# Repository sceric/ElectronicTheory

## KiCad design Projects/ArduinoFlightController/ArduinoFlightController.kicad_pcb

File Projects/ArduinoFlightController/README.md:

# ArduinoFlightController
Flight controller hardware using mulitiwii firmware

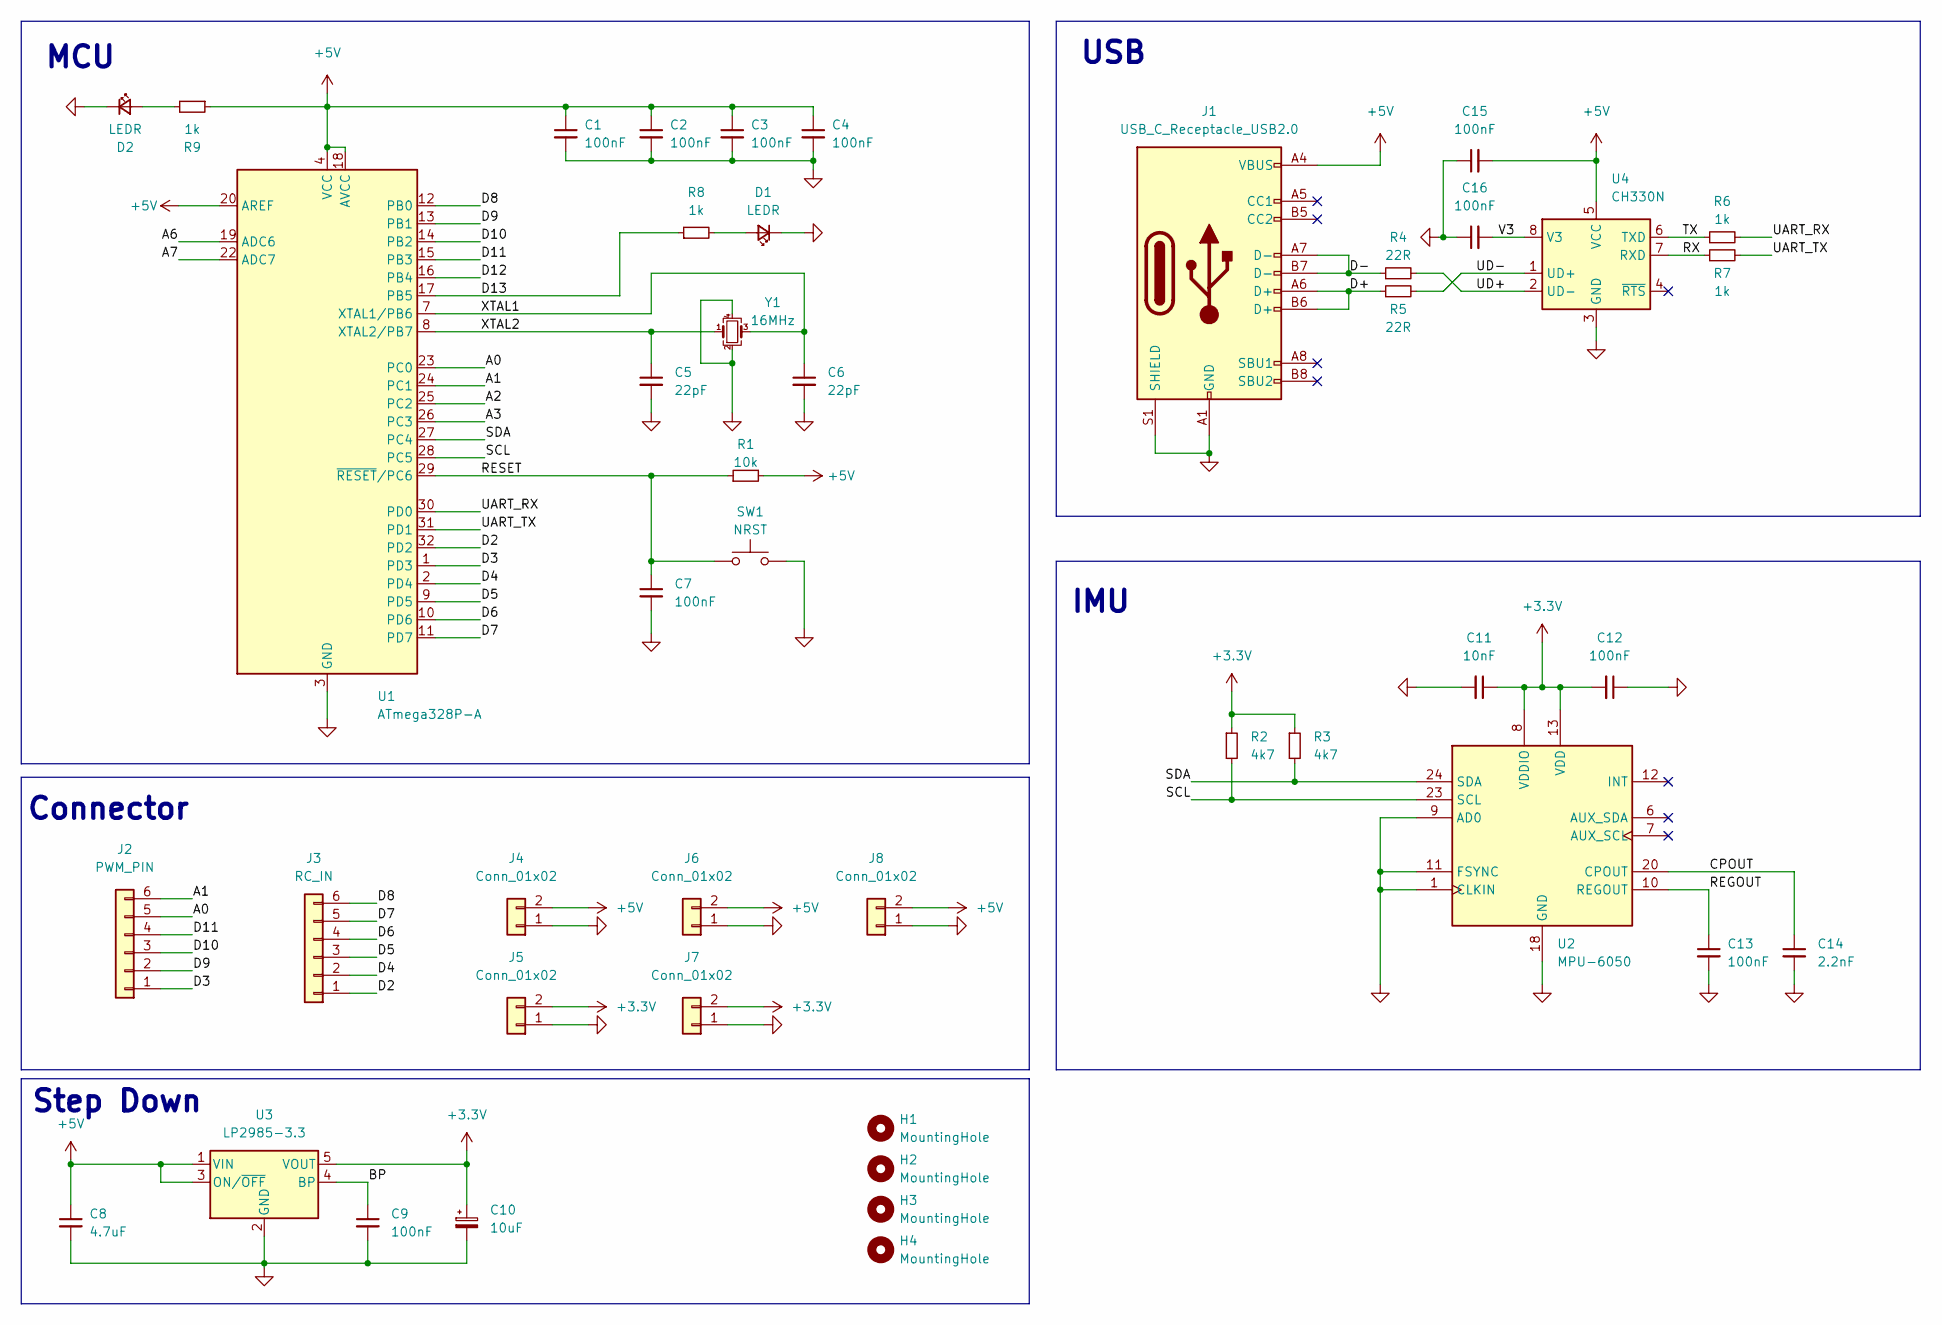
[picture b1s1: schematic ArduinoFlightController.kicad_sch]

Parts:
C1, C2, C3, C4, C7, C9, C12, C13, C15, C16: 100nF; C_0603_1608Metric
C5, C6: 22pF; C_0603_1608Metric
C8: 4.7uF; C_0805_2012Metric
C10: 10uF; CP_EIA-3216-10_Kemet-I
C11: 10nF; C_0603_1608Metric
C14: 2.2nF; C_0603_1608Metric
D1, D2: LEDR; LED_0603_1608Metric
H1, H2, H3, H4: MountingHole; MountingHole_3mm_Pad_Via
J1: USB_C_Receptacle_USB2.0; USB_C_Receptacle_XKB_U262-16XN-4BVC11
J2: PWM_PIN; pad_01x06
J3: RC_IN; pad_01x06
J4, J5, J6, J7, J8: Conn_01x02; pad_01x02
R1: 10k; R_0603_1608Metric
R2, R3: 4k7; R_0603_1608Metric
R4, R5: 22R; R_0603_1608Metric
R6, R7, R8, R9: 1k; R_0603_1608Metric
SW1: NRST; SW_SPST_B3U-1000P
U1: ATmega328P-A; TQFP-32_7x7mm_P0.8mm
U2: MPU-6050; InvenSense_QFN-24_4x4mm_P0.5mm
U3: LP2985-3.3; SOT-23-5
U4: CH330N; SOIC-8_3.9x4.9mm_P1.27mm
Y1: 16MHz; Crystal_SMD_3225-4Pin_3.2x2.5mm

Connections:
+3V3: C10.1, C11.1, C12.2, J5.2, J7.2, R2.1, R3.1, U2.8 (VDDIO), U2.13 (VDD), U3.5 (VOUT)
+5V: C1.1, C2.1, C3.1, C4.1, C8.1, C15.2, J1.A4 (VBUS), J1.A9 (VBUS), J1.B4 (VBUS), J1.B9 (VBUS), J4.2, J6.2, J8.2, R1.2, R9.1, U1.4 (VCC), U1.6 (VCC), U1.18 (AVCC), U1.20 (AREF), U3.1 (VIN), U3.3 (ON/~OFF), U4.5 (VCC)
/A0: J2.5, U1.23 (PC0)
/A1: J2.6, U1.24 (PC1)
/A2: U1.25 (PC2)
/A3: U1.26 (PC3)
/A6: U1.19 (ADC6)
/A7: U1.22 (ADC7)
/BP: C9.1, U3.4 (BP)
/CPOUT: C14.1, U2.20 (CPOUT)
/D2: J3.1, U1.32 (PD2)
/D3: J2.1, U1.1 (PD3)
/D4: J3.2, U1.2 (PD4)
/D5: J3.3, U1.9 (PD5)
/D6: J3.4, U1.10 (PD6)
/D7: J3.5, U1.11 (PD7)
/D8: J3.6, U1.12 (PB0)
/D9: J2.2, U1.13 (PB1)
/D10: J2.3, U1.14 (PB2)
/D11: J2.4, U1.15 (PB3)
/D12: U1.16 (PB4)
/D13: R8.1, U1.17 (PB5)
/D+: J1.A6 (D+), J1.B6 (D+), R5.1
/D-: J1.A7 (D-), J1.B7 (D-), R4.1
/REGOUT: C13.1, U2.10 (REGOUT)
/RESET: C7.1, R1.1, SW1.1, U1.29 (~RESET/PC6)
/RX: R7.1, U4.7 (RXD)
/SCL: R2.2, U1.28 (PC5), U2.23 (SCL)
/SDA: R3.2, U1.27 (PC4), U2.24 (SDA)
/TX: R6.1, U4.6 (TXD)
/UART_RX: R6.2, U1.30 (PD0)
/UART_TX: R7.2, U1.31 (PD1)
/UD+: R4.2, U4.2 (UD-)
/UD-: R5.2, U4.1 (UD+)
/V3: C16.2, U4.8 (V3)
/XTAL1: C6.1, U1.7 (XTAL1/PB6), Y1.3
/XTAL2: C5.1, U1.8 (XTAL2/PB7), Y1.1
GND: C1.2, C2.2, C3.2, C4.2, C5.2, C6.2, C7.2, C8.2, C9.2, C10.2, C11.2, C12.1, C13.2, C14.2, C15.1, C16.1, D1.1 (K), D2.1 (K), J1.A1 (GND), J1.A12 (GND), J1.B1 (GND), J1.B12 (GND), J1.S1 (SHIELD), J4.1, J5.1, J6.1, J7.1, J8.1, SW1.2, U1.3 (GND), U1.5 (GND), U1.21 (GND), U2.1 (CLKIN), U2.9 (AD0), U2.11 (FSYNC), U2.18 (GND), U3.2 (GND), U4.3 (GND), Y1.2, Y1.4
unnamed: D1.2 (A), R8.2
unnamed: D2.2 (A), R9.2

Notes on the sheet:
USB
MCU
Step Down
IMU
Connector

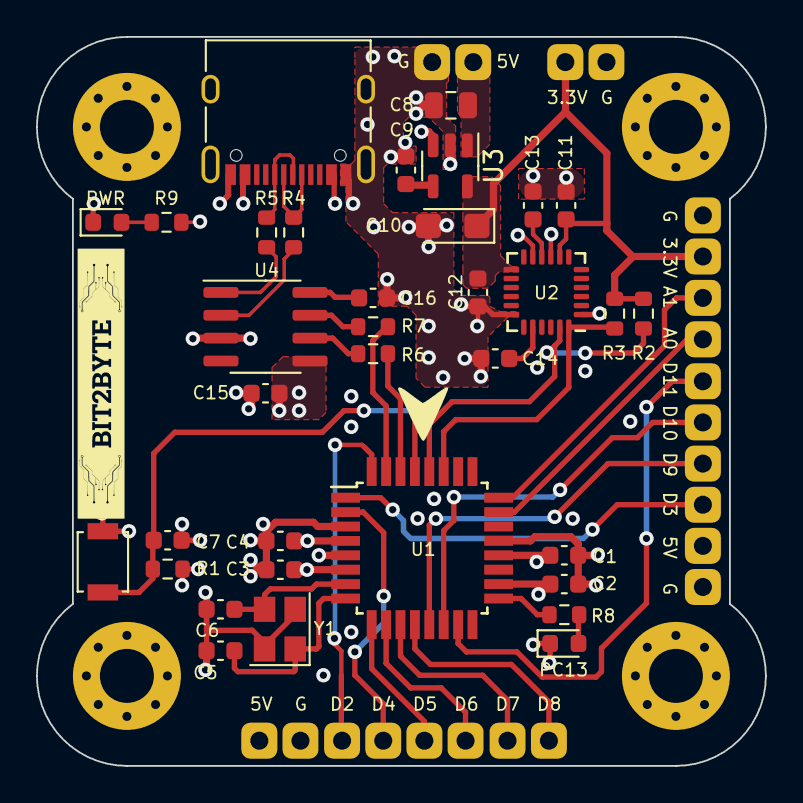
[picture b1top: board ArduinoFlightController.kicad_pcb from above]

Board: 4 copper layers, 40.5 x 40.5 mm, 45 parts (0 on the bottom side), 35 nets.

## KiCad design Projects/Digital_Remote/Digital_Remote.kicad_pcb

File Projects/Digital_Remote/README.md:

# Digital_Remote
Wireless transmitter based on AS01-SPIPX (NRF)

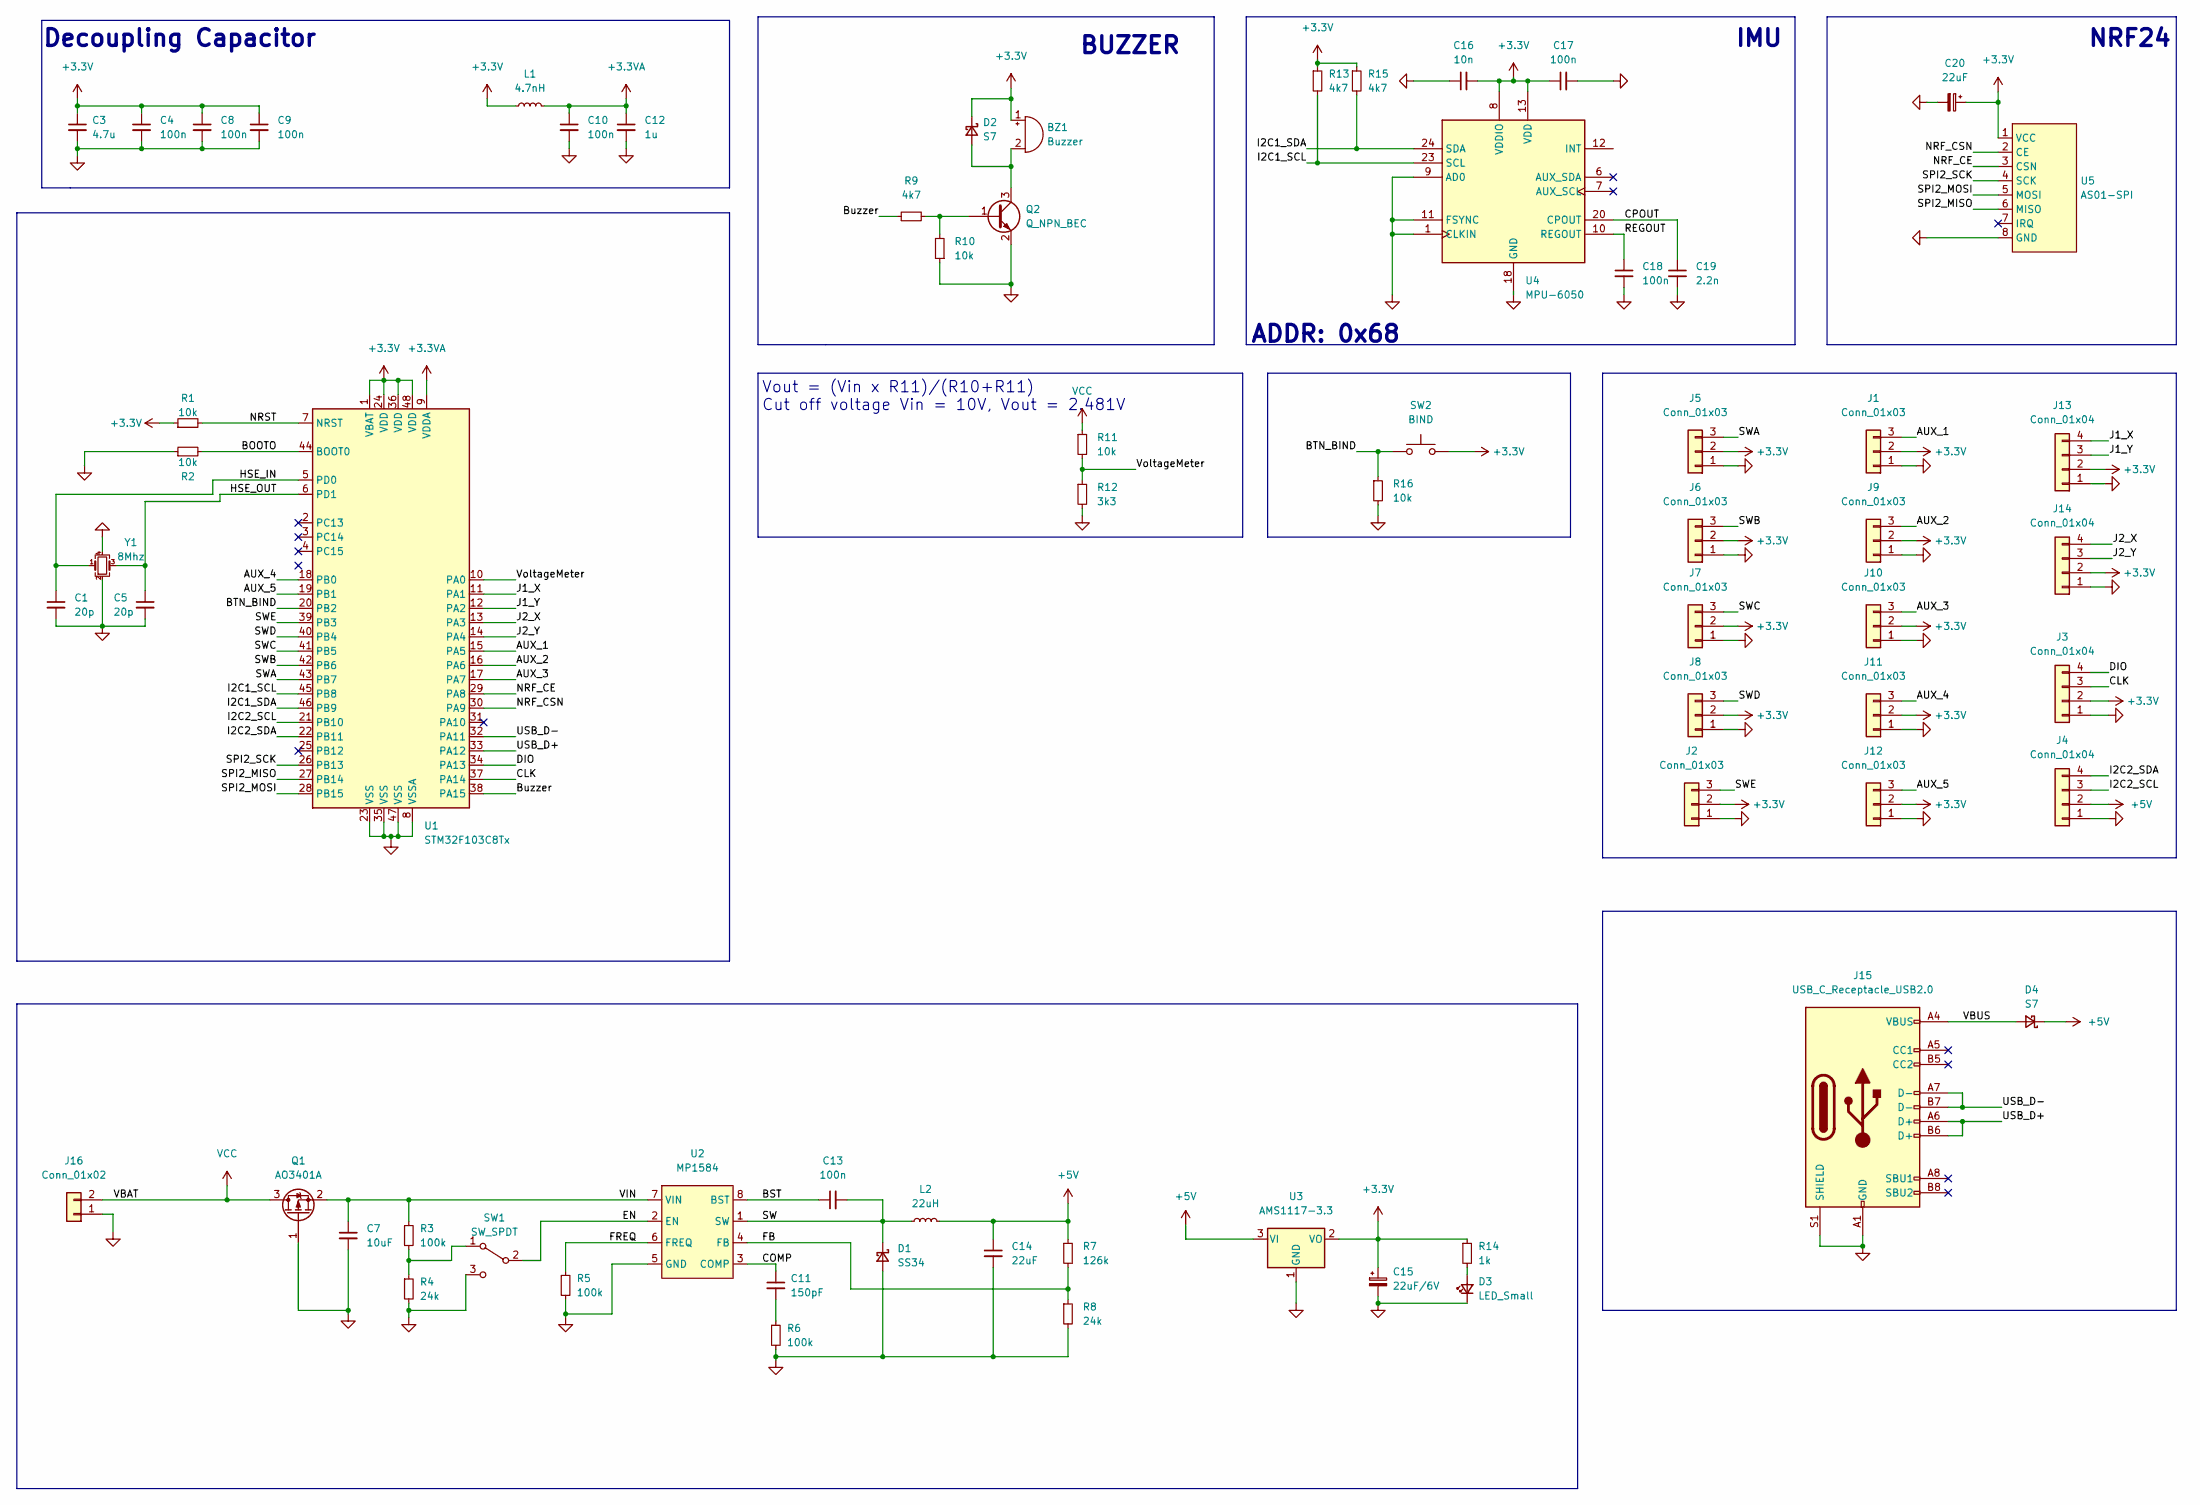
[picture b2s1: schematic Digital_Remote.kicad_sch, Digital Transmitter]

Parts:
BZ1: Buzzer; Buzzer_12x9.5RM7.6
C1, C5: 20p; C_0603_1608Metric
C3: 4.7u; C_0805_2012Metric
C4, C8, C9, C10, C13, C17, C18: 100n; C_0603_1608Metric
C7: 10uF; C_1206_3216Metric
C11: 150pF; C_0603_1608Metric
C12: 1u; C_0603_1608Metric
C14: 22uF; C_1206_3216Metric
C15: 22uF/6V; CP_EIA-3216-10_Kemet-I
C16: 10n; C_0603_1608Metric
C19: 2.2n; C_0603_1608Metric
C20: 22uF; CP_EIA-3216-10_Kemet-I
D1: SS34; D_SMA
D2, D4: S7; D_SOD-123
D3: LED_Small; LED_0603_1608Metric
J1, J2, J5, J6, J7, J8, J9, J10, J11, J12: Conn_01x03; con_01x03_W2.5mm-H2.5mm
J3, J4, J13, J14: Conn_01x04; con_01x04_W2.5mm-H2.5mm
J15: USB_C_Receptacle_USB2.0; USB_C_Receptacle_XKB_U262-16XN-4BVC11
J16: Conn_01x02; PinHeader_1x02_P2.54mm_Vertical
L1: 4.7nH; L_0603_1608Metric
L2: 22uH; L_7.3x7.3_H4.5
Q1: AO3401A; SOT-23
Q2: Q_NPN_BEC; SOT-23
R1, R2, R10, R11, R16: 10k; R_0603_1608Metric
R3, R5, R6: 100k; R_0603_1608Metric
R4, R8: 24k; R_0603_1608Metric
R7: 126k; R_0603_1608Metric
R9, R13, R15: 4k7; R_0603_1608Metric
R12: 3k3; R_0603_1608Metric
R14: 1k; R_0603_1608Metric
SW1: SW_SPDT; SW_CuK_JS202011CQN_DPDT_Straight
SW2: BIND; SW_PUSH_6mm_H5mm
U1: STM32F103C8Tx; LQFP-48_7x7mm_P0.5mm
U2: MP1584; SOIC-8-1EP_3.9x4.9mm_P1.27mm_EP2.41x3.81mm
U3: AMS1117-3.3; SOT-223-3_TabPin2
U4: MPU-6050; InvenSense_QFN-24_4x4mm_P0.5mm
U5: AS01-SPI; AS01-SPIPX-NRF24
Y1: 8Mhz; Crystal_SMD_3225-4Pin_3.2x2.5mm

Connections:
+3.3VA: C10.1, C12.1, L1.2, U1.9 (VDDA)
+3V3: BZ1.1 (-), C3.1, C4.1, C8.1, C9.1, C15.1, C16.2, C17.1, C20.1, D2.1 (K), J1.2, J2.2, J3.2, J5.2, J6.2, J7.2, J8.2, J9.2, J10.2, J11.2, J12.2, J13.2, J14.2, L1.1, R1.1, R13.1, R14.1, R15.1, SW2.2, U1.1 (VBAT), U1.24 (VDD), U1.36 (VDD), U1.48 (VDD), U3.2 (VO), U4.8 (VDDIO), U4.13 (VDD), U5.1 (VCC)
+5V: C14.1, D4.1 (K), J4.2, L2.2, R7.1, U3.3 (VI)
/AUX_1: J1.3, U1.15 (PA5)
/AUX_2: J9.3, U1.16 (PA6)
/AUX_3: J10.3, U1.17 (PA7)
/AUX_4: J11.3, U1.18 (PB0)
/AUX_5: J12.3, U1.19 (PB1)
/BOOTO: R2.2, U1.44 (BOOT0)
/BST: C13.1, U2.8 (BST)
/BTN_BIND: R16.1, SW2.1, U1.20 (PB2)
/Buzzer: R9.1, U1.38 (PA15)
/CLK: J3.3, U1.37 (PA14)
/COMP: C11.1, U2.3 (COMP)
/CPOUT: C19.1, U4.20 (CPOUT)
/DIO: J3.4, U1.34 (PA13)
/EN: SW1.2 (B), U2.2 (EN)
/FB: R7.2, R8.1, U2.4 (FB)
/FREQ: R5.1, U2.6 (FREQ)
/HSE_IN: C1.1, U1.5 (PD0), Y1.1
/HSE_OUT: C5.1, U1.6 (PD1), Y1.3
/I2C1_SCL: R13.2, U1.45 (PB8), U4.23 (SCL)
/I2C1_SDA: R15.2, U1.46 (PB9), U4.24 (SDA)
/I2C2_SCL: J4.3, U1.21 (PB10)
/I2C2_SDA: J4.4, U1.22 (PB11)
/J1_X: J13.4, U1.11 (PA1)
/J1_Y: J13.3, U1.12 (PA2)
/J2_X: J14.4, U1.13 (PA3)
/J2_Y: J14.3, U1.14 (PA4)
/NRF_CE: U1.29 (PA8), U5.3 (CSN)
/NRF_CSN: U1.30 (PA9), U5.2 (CE)
/NRST: R1.2, U1.7 (NRST)
/REGOUT: C18.1, U4.10 (REGOUT)
/SPI2_MISO: U1.27 (PB14), U5.6 (MISO)
/SPI2_MOSI: U1.28 (PB15), U5.5 (MOSI)
/SPI2_SCK: U1.26 (PB13), U5.4 (SCK)
/SW: C13.2, D1.1 (K), L2.1, U2.1 (SW)
/SWA: J5.3, U1.43 (PB7)
/SWB: J6.3, U1.42 (PB6)
/SWC: J7.3, U1.41 (PB5)
/SWD: J8.3, U1.40 (PB4)
/SWE: J2.3, U1.39 (PB3)
/USB_D+: J15.A6 (D+), J15.B6 (D+), U1.33 (PA12)
/USB_D-: J15.A7 (D-), J15.B7 (D-), U1.32 (PA11)
/VBUS: D4.2 (A), J15.A4 (VBUS), J15.A9 (VBUS), J15.B4 (VBUS), J15.B9 (VBUS)
/VIN: C7.1, Q1.2 (S), R3.1, U2.7 (VIN)
/VoltageMeter: R11.2, R12.1, U1.10 (PA0)
GND: C1.2, C3.2, C4.2, C5.2, C7.2, C8.2, C9.2, C10.2, C12.2, C14.2, C15.2, C16.1, C17.2, C18.2, C19.2, C20.2, D1.2 (A), D3.1 (K), J1.1, J2.1, J3.1, J4.1, J5.1, J6.1, J7.1, J8.1, J9.1, J10.1, J11.1, J12.1, J13.1, J14.1, J15.A1 (GND), J15.A12 (GND), J15.B1 (GND), J15.B12 (GND), J15.S1 (SHIELD), J16.1, Q1.1 (G), Q2.2 (E), R2.1, R4.2, R5.2, R6.2, R8.2, R10.1, R12.2, R16.2, SW1.3 (C), U1.8 (VSSA), U1.23 (VSS), U1.35 (VSS), U1.47 (VSS), U2.5 (GND), U3.1 (GND), U4.1 (CLKIN), U4.9 (AD0), U4.11 (FSYNC), U4.18 (GND), U5.8 (GND), Y1.2, Y1.4
unnamed: BZ1.2 (+), D2.2 (A), Q2.3 (C)
unnamed: C11.2, R6.1
unnamed: D3.2 (A), R14.2
unnamed: Q2.1 (B), R9.2, R10.2
unnamed: R3.2, R4.1, SW1.1 (A)
VCC: J16.2, Q1.3 (D), R11.1

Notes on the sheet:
Vout = (Vin x R11)/(R10+R11)
Cut off voltage Vin = 10V, Vout = 2.481V
NRF24
BUZZER
Decoupling Capacitor
ADDR: 0x68
IMU

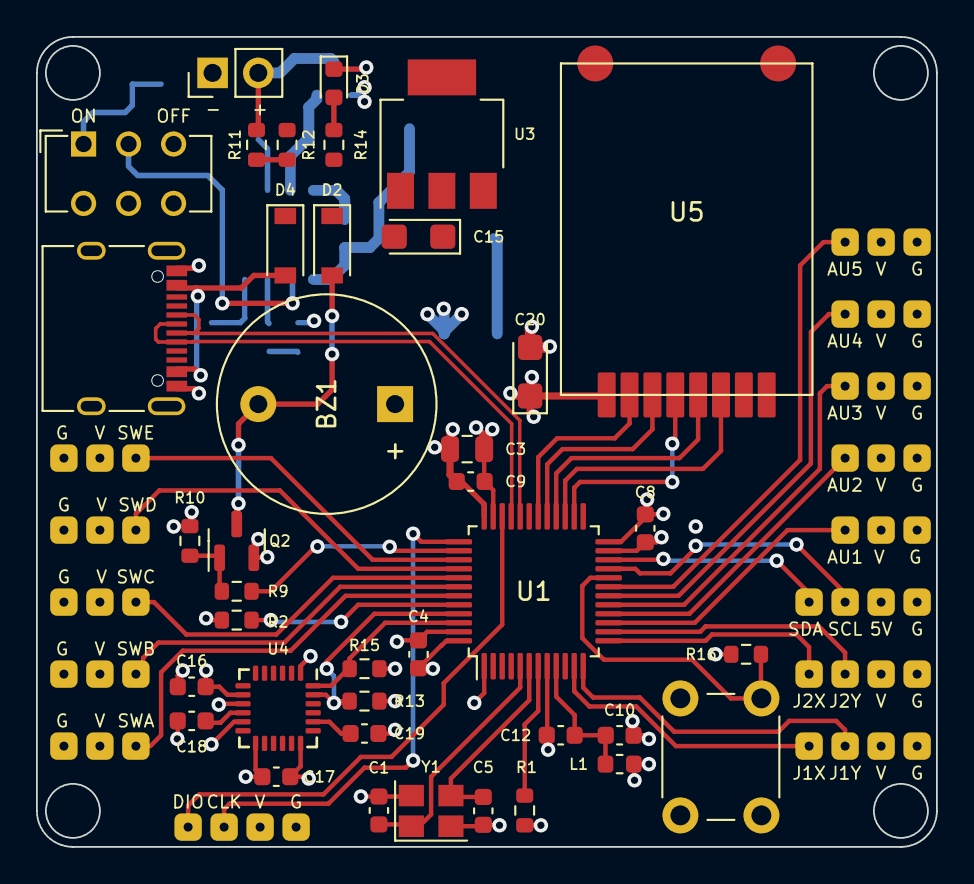
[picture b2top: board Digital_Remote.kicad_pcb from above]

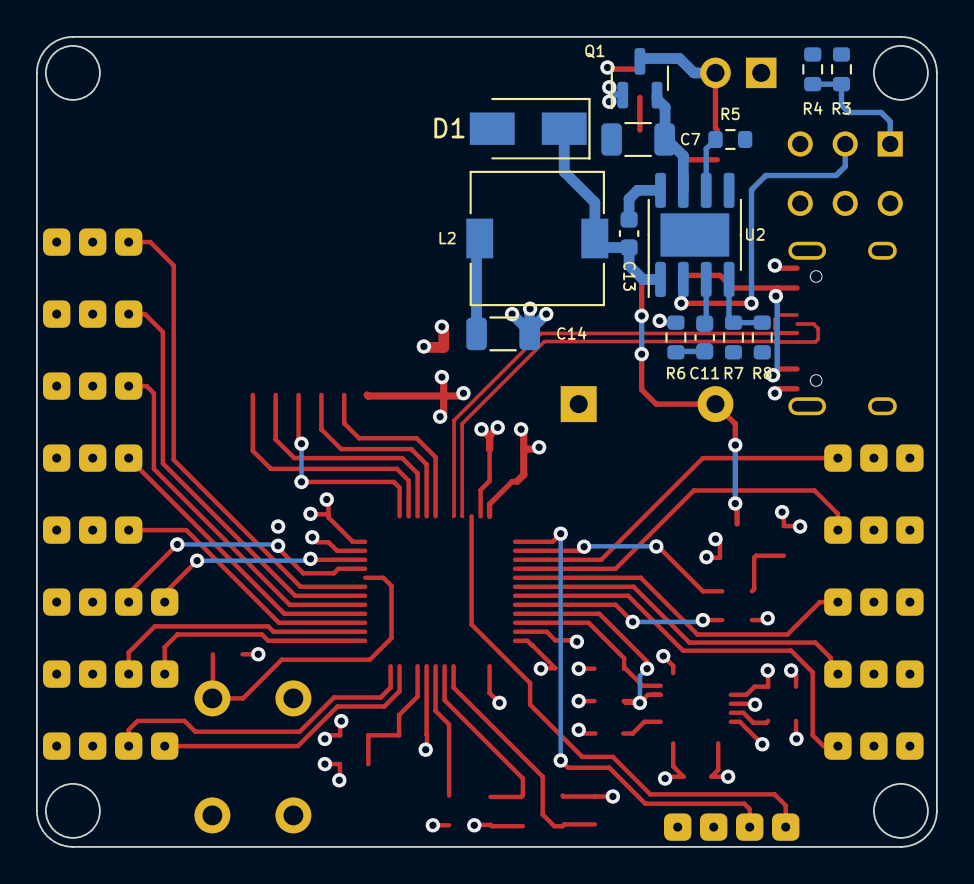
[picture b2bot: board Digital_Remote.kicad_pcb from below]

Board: 4 copper layers, 50.0 x 45.0 mm, 67 parts (14 on the bottom side), 54 nets.

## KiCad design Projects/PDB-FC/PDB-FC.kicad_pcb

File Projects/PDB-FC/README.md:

# PDB-FC
Power Delivery Board for flight controller

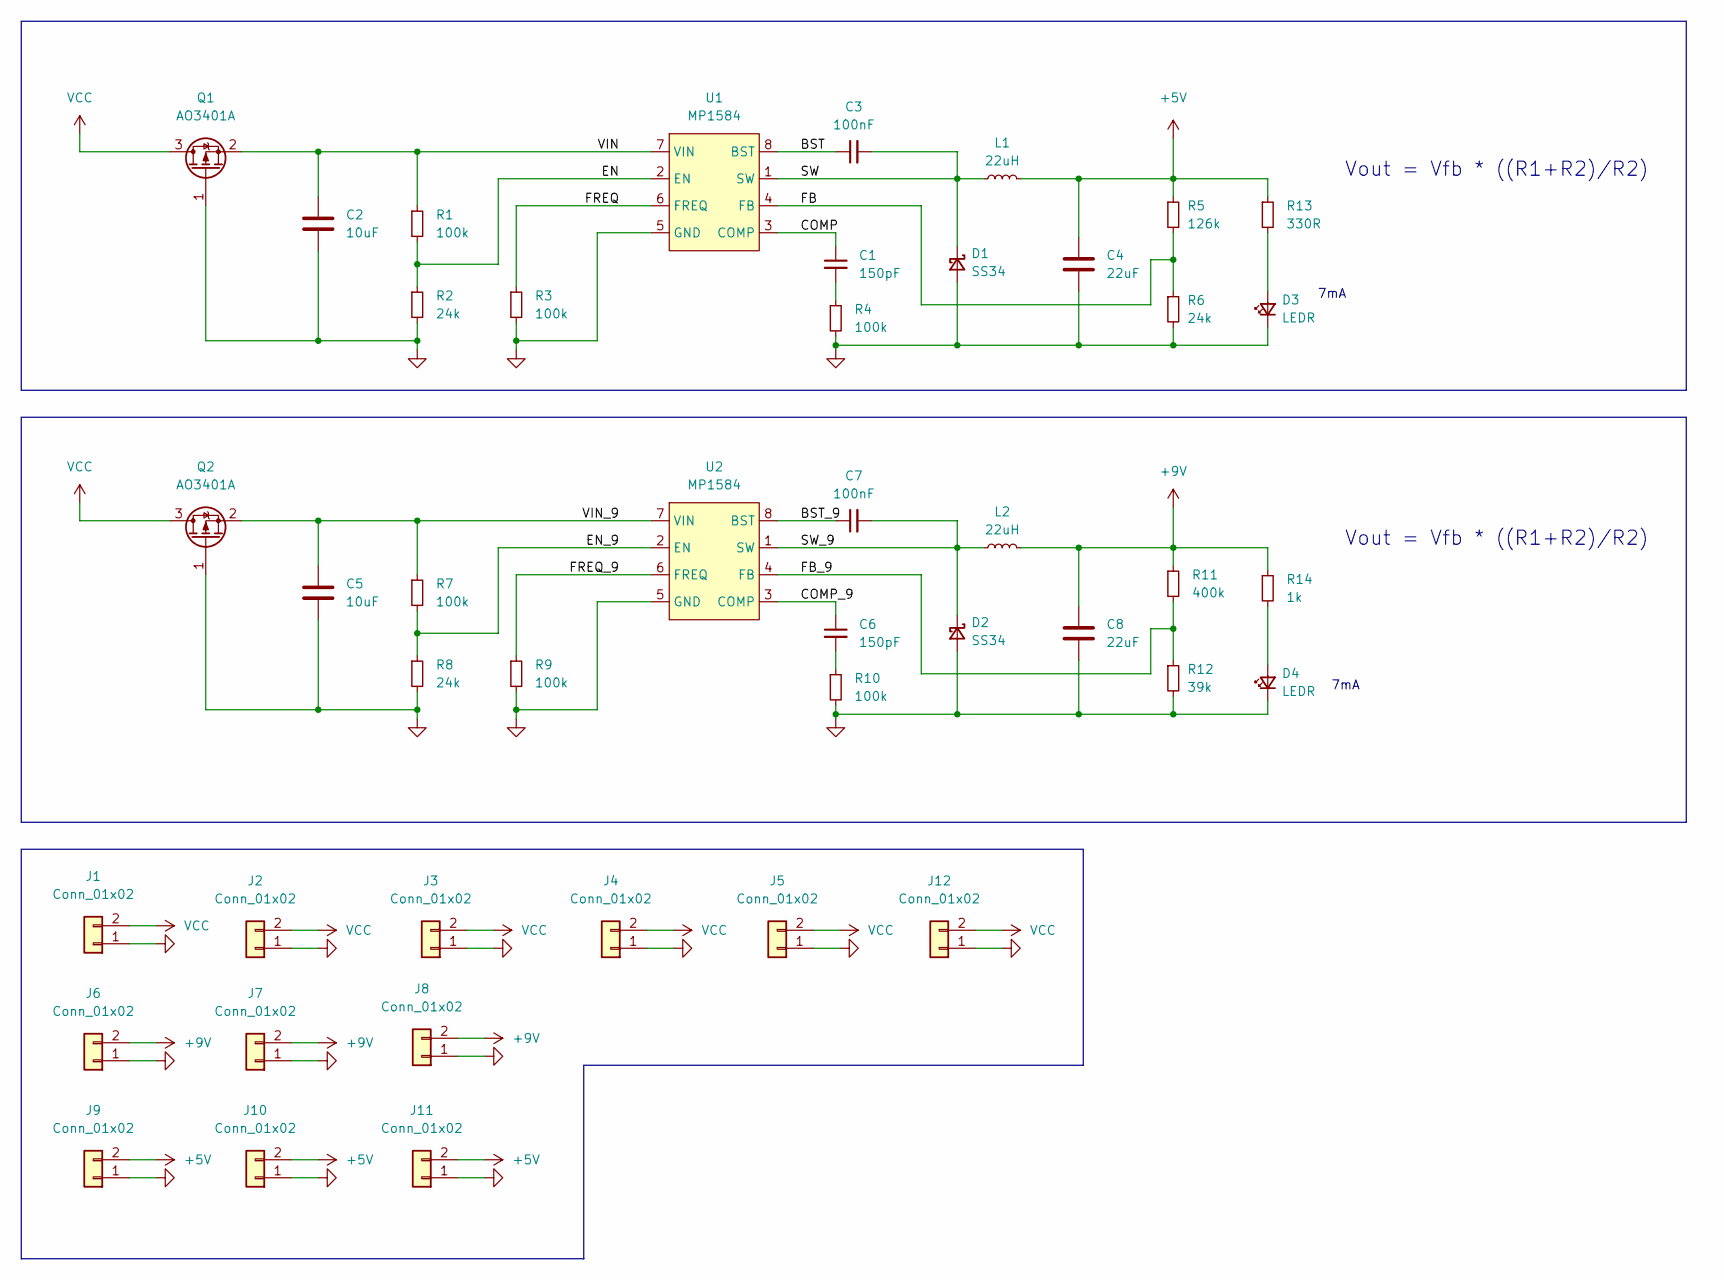
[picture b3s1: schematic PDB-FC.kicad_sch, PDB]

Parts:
C1, C6: 150pF; C_0603_1608Metric
C2, C5: 10uF; C_1206_3216Metric
C3, C7: 100nF; C_0603_1608Metric
C4, C8: 22uF; C_1206_3216Metric
D1, D2: SS34; D_SMA
D3, D4: LEDR; LED_0603_1608Metric
J1, J12: Conn_01x02; PDB_6mm
J2, J3, J4, J5: Conn_01x02; PDB_Pad01x02
J6, J7, J8, J9, J10, J11: Conn_01x02; ConPadx02-1.5mm
L1, L2: 22uH; L_7.3x7.3_H4.5
Q1, Q2: AO3401A; SOT-23
R1, R3, R4, R7, R9, R10: 100k; R_0603_1608Metric
R2, R6, R8: 24k; R_0603_1608Metric
R5: 126k; R_0603_1608Metric
R11: 400k; R_0603_1608Metric
R12: 39k; R_0603_1608Metric
R13: 330R; R_0603_1608Metric
R14: 1k; R_0603_1608Metric
U1, U2: MP1584; SOIC-8-1EP_3.9x4.9mm_P1.27mm_EP2.41x3.3mm

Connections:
+5V: C4.1, J9.2, J10.2, J11.2, L1.2, R5.1, R13.1
+9V: C8.1, J6.2, J7.2, J8.2, L2.2, R11.1, R14.1
/BST: C3.1, U1.8 (BST)
/BST_9: C7.1, U2.8 (BST)
/COMP: C1.1, U1.3 (COMP)
/COMP_9: C6.1, U2.3 (COMP)
/EN: R1.2, R2.1, U1.2 (EN)
/EN_9: R7.2, R8.1, U2.2 (EN)
/FB: R5.2, R6.1, U1.4 (FB)
/FB_9: R11.2, R12.1, U2.4 (FB)
/FREQ: R3.1, U1.6 (FREQ)
/FREQ_9: R9.1, U2.6 (FREQ)
/SW: C3.2, D1.1 (K), L1.1, U1.1 (SW)
/SW_9: C7.2, D2.1 (K), L2.1, U2.1 (SW)
/VIN: C2.1, Q1.2 (S), R1.1, U1.7 (VIN)
/VIN_9: C5.1, Q2.2 (S), R7.1, U2.7 (VIN)
GND: C2.2, C4.2, C5.2, C8.2, D1.2 (A), D2.2 (A), D3.1 (K), D4.1 (K), J1.1, J2.1, J3.1, J4.1, J5.1, J6.1, J7.1, J8.1, J9.1, J10.1, J11.1, J12.1, Q1.1 (G), Q2.1 (G), R2.2, R3.2, R4.2, R6.2, R8.2, R9.2, R10.2, R12.2, U1.5 (GND), U2.5 (GND)
unnamed: C1.2, R4.1
unnamed: C6.2, R10.1
unnamed: D3.2 (A), R13.2
unnamed: D4.2 (A), R14.2
VCC: J1.2, J2.2, J3.2, J4.2, J5.2, J12.2, Q1.3 (D), Q2.3 (D)

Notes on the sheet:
7mA
Vout = Vfb * ((R1+R2)/R2)

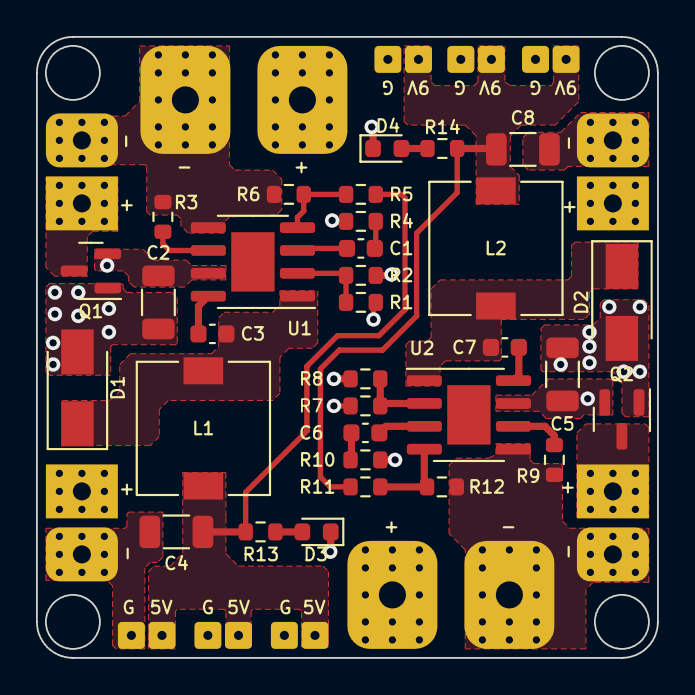
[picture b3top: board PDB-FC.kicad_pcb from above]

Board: 4 copper layers, 34.5 x 34.5 mm, 44 parts (0 on the bottom side), 22 nets.

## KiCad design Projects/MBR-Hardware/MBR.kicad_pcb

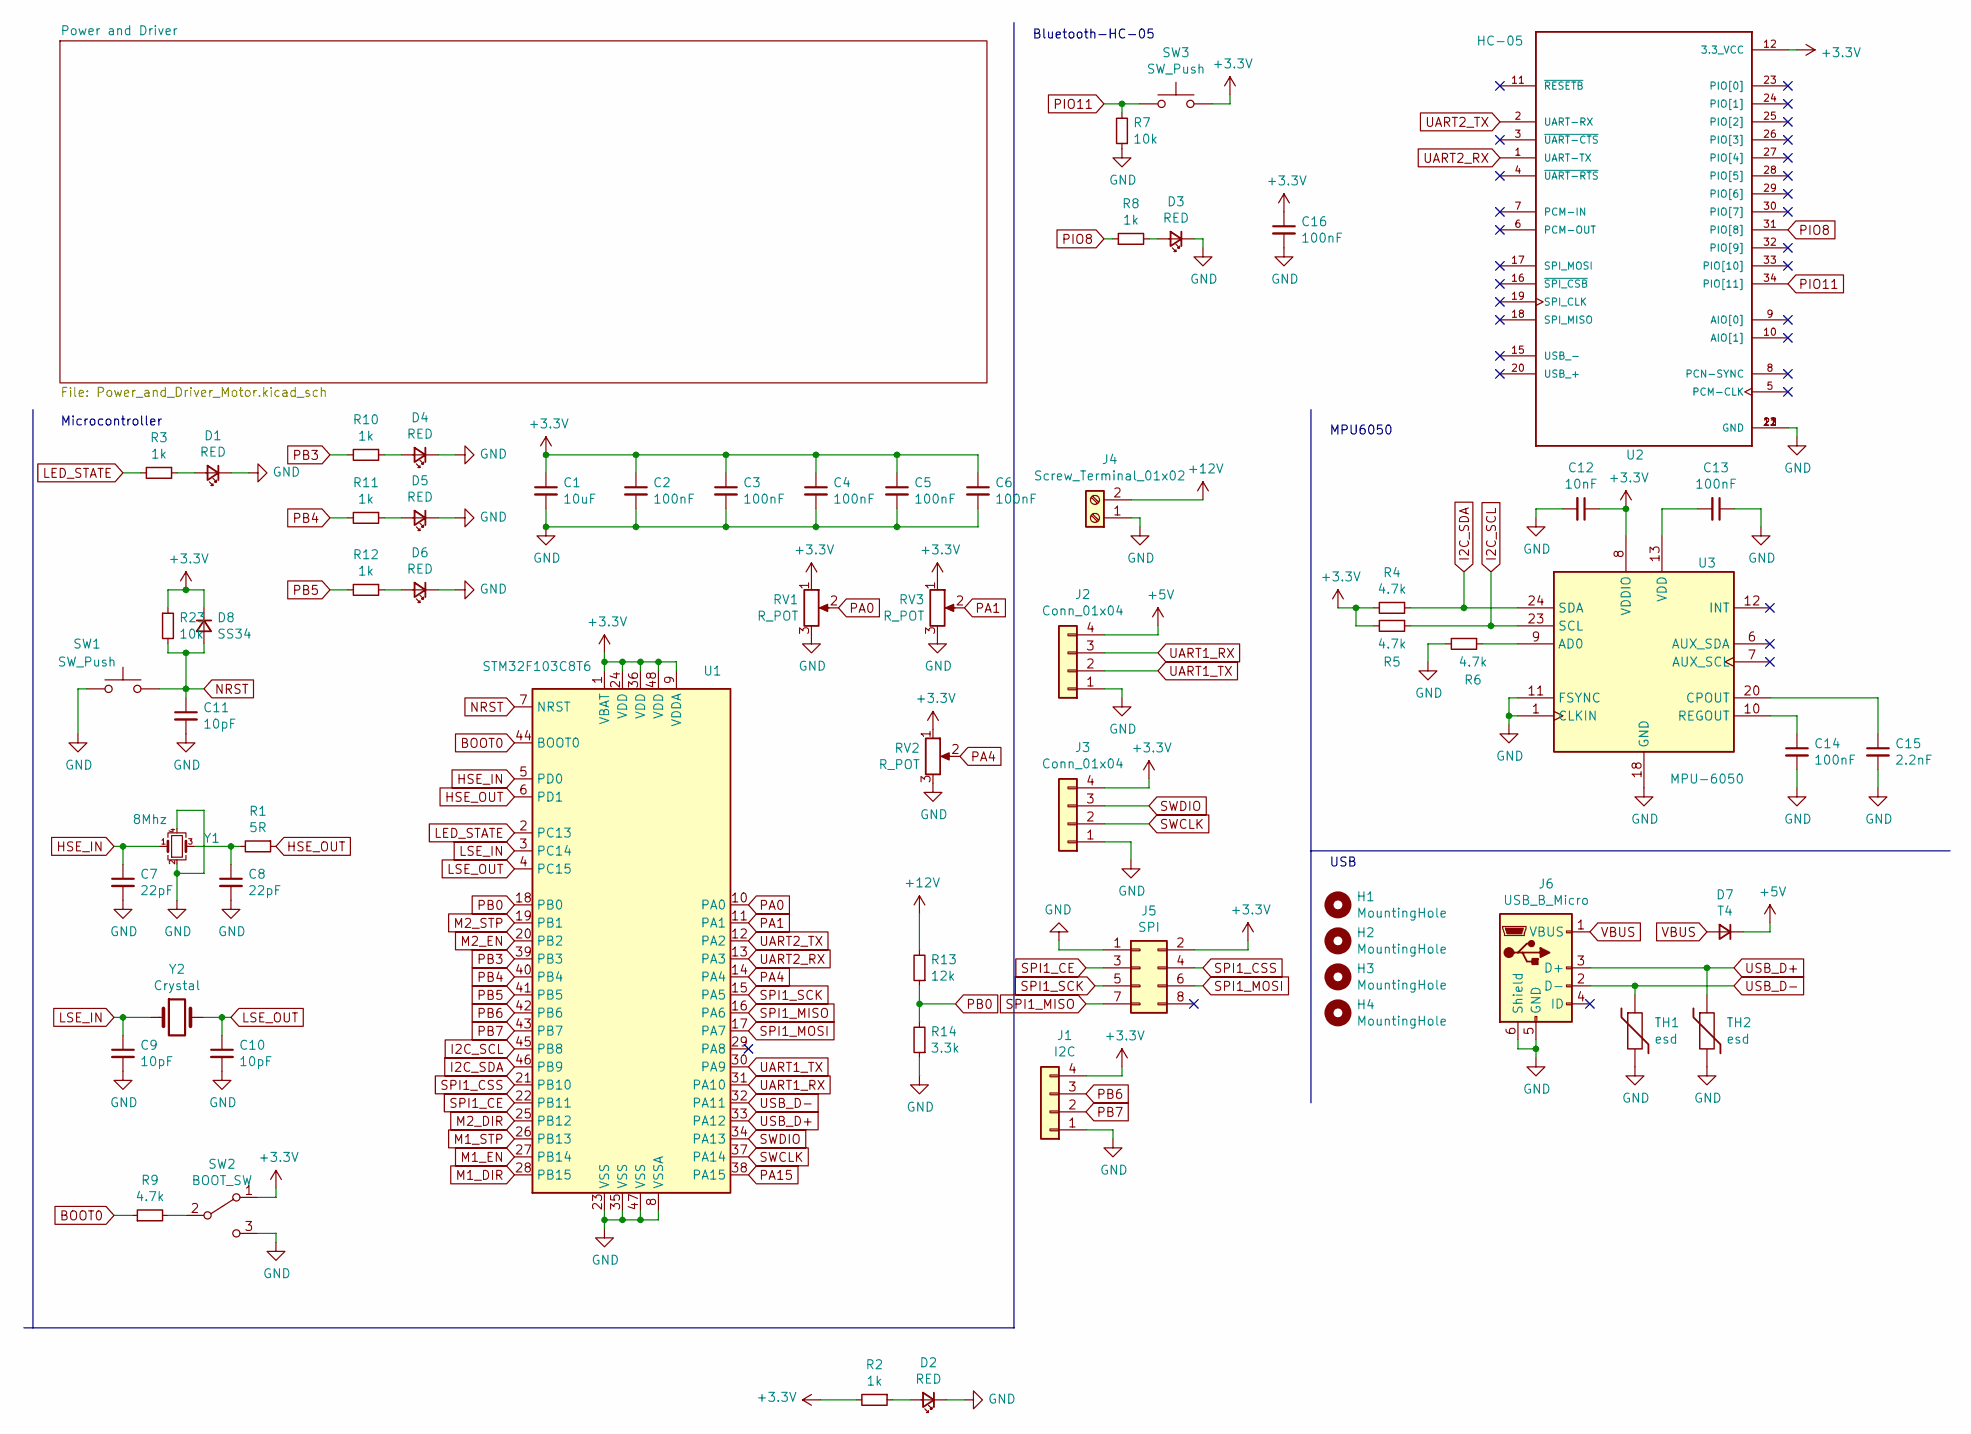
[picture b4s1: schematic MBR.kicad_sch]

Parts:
C1: 10uF; C_0805_2012Metric
C2, C3, C4, C5, C6, C13, C14, C16: 100nF; C_0603_1608Metric
C7, C8: 22pF; C_0603_1608Metric
C9, C10, C11: 10pF; C_0603_1608Metric
C12: 10nF; C_0603_1608Metric
C15: 2.2nF; C_0603_1608Metric
D1, D2, D3, D4, D5, D6: RED; LED_0603_1608Metric
D7: T4; D_SOD-123
D8: SS34
H1, H2, H3, H4: MountingHole; MountingHole_3.2mm_M3_Pad_Via
J1: I2C; JST_EH_B4B-EH-A_1x04_P2.50mm_Vertical
J2, J3: Conn_01x04; JST_EH_B4B-EH-A_1x04_P2.50mm_Vertical
J4: Screw_Terminal_01x02; TerminalBlock_bornier-2_P5.08mm
J5: SPI; PinHeader_2x04_P2.54mm_Vertical
J6: USB_B_Micro; USB_Micro-B_Molex-105017-0001
R1: 5R; R_0603_1608Metric
R2, R3, R8, R10, R11, R12: 1k; R_0603_1608Metric
R4, R5, R6, R9: 4.7k; R_0603_1608Metric
R7: 10k; R_0603_1608Metric
R13: 12k; R_0603_1608Metric
R14: 3.3k; R_0603_1608Metric
R23: 10k
RV1, RV2, RV3: R_POT; Potentiometer_Vishay_T73YP_Vertical
SW1, SW3: SW_Push; SW_SPST_TL3342
SW2: BOOT_SW; SW_SPDT_PCM12
TH1, TH2: esd; D_0603_1608Metric
U1: STM32F103C8T6; LQFP-48_7x7mm_P0.5mm
U2: HC-05; XCVR_HC-05
U3: MPU-6050; InvenSense_QFN-24_4x4mm_P0.5mm
Y1: 8Mhz; Crystal_SMD_3225-4Pin_3.2x2.5mm
Y2: Crystal; Crystal_C26-LF_D2.1mm_L6.5mm_Horizontal

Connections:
+3V3: C1.1, C2.1, C3.1, C4.1, C5.1, C6.1, C12.1, C16.1, D8.1 (K), J1.4, J3.4, J5.2, R2.2, R4.2, R5.2, R23.1, RV1.1, RV2.1, RV3.1, SW2.1 (A), SW3.2, U1.1 (VBAT), U1.9 (VDDA), U1.24 (VDD), U1.36 (VDD), U1.48 (VDD), U2.12 (3.3_VCC), U3.8 (VDDIO); also elsewhere on the board
+5V: D7.1 (K), J2.4; also elsewhere on the board
+12V: J4.2, R13.2; also elsewhere on the board
BOOT0: R9.1, U1.44 (BOOT0)
GND: C1.2, C2.2, C3.2, C4.2, C5.2, C6.2, C7.2, C8.2, C9.2, C10.2, C11.2, C12.2, C13.1, C14.2, C15.2, C16.2, D1.1 (K), D2.1 (K), D3.1 (K), D4.1 (K), D5.1 (K), D6.1 (K), J1.1, J2.1, J3.1, J4.1, J5.1, J6.5 (GND), J6.6 (Shield), R6.2, R7.1, R14.1, RV1.3, RV2.3, RV3.3, SW1.1, SW2.3 (C), TH1.2, TH2.2, U1.8 (VSSA), U1.23 (VSS), U1.35 (VSS), U1.47 (VSS), U2.13 (GND), U2.21 (GND), U2.22 (GND), U3.1 (CLKIN), U3.11 (FSYNC), U3.18 (GND), Y1.2, Y1.4; also elsewhere on the board
HSE_IN: C7.1, U1.5 (PD0), Y1.1
HSE_OUT: R1.1, U1.6 (PD1)
I2C_SCL: R5.1, U1.45 (PB8), U3.23 (SCL)
I2C_SDA: R4.1, U1.46 (PB9), U3.24 (SDA)
LED_STATE: R3.2, U1.2 (PC13)
LSE_IN: C9.1, U1.3 (PC14), Y2.1
LSE_OUT: C10.1, U1.4 (PC15), Y2.2
M1_DIR: U1.28 (PB15); also elsewhere on the board
M1_EN: U1.27 (PB14); also elsewhere on the board
M1_STP: U1.26 (PB13); also elsewhere on the board
M2_DIR: U1.25 (PB12); also elsewhere on the board
M2_EN: U1.20 (PB2); also elsewhere on the board
M2_STP: U1.19 (PB1); also elsewhere on the board
NRST: C11.1, D8.2 (A), R23.2, SW1.2, U1.7 (NRST)
unnamed: C8.1, R1.2, Y1.3
unnamed: C13.2, U3.13 (VDD)
unnamed: C14.1, U3.10 (REGOUT)
unnamed: C15.1, U3.20 (CPOUT)
unnamed: D1.2 (A), R3.1
unnamed: D2.2 (A), R2.1
unnamed: D3.2 (A), R8.2
unnamed: D4.2 (A), R10.1
unnamed: D5.2 (A), R11.1
unnamed: D6.2 (A), R12.1
unnamed: R6.1, U3.9 (AD0)
unnamed: R9.2, SW2.2 (B)
PA0: RV1.2, U1.10 (PA0)
PA1: RV3.2, U1.11 (PA1)
PA4: RV2.2, U1.14 (PA4)
PA15: U1.38 (PA15)
PB0: R13.1, R14.2, U1.18 (PB0)
PB3: R10.2, U1.39 (PB3)
PB4: R11.2, U1.40 (PB4)
PB5: R12.2, U1.41 (PB5)
PB6: J1.3, U1.42 (PB6)
PB7: J1.2, U1.43 (PB7)
PIO8: R8.1, U2.31 (PIO[8])
PIO11: R7.2, SW3.1, U2.34 (PIO[11])
SPI1_CE: J5.3, U1.22 (PB11)
SPI1_CSS: J5.4, U1.21 (PB10)
SPI1_MISO: J5.7, U1.16 (PA6)
SPI1_MOSI: J5.6, U1.17 (PA7)
SPI1_SCK: J5.5, U1.15 (PA5)
SWCLK: J3.2, U1.37 (PA14)
SWDIO: J3.3, U1.34 (PA13)
UART1_RX: J2.3, U1.31 (PA10)
UART1_TX: J2.2, U1.30 (PA9)
UART2_RX: U1.13 (PA3), U2.1 (UART-TX)
UART2_TX: U1.12 (PA2), U2.2 (UART-RX)
USB_D+: J6.3 (D+), TH2.1, U1.33 (PA12)
USB_D-: J6.2 (D-), TH1.1, U1.32 (PA11)
VBUS: D7.2 (A), J6.1 (VBUS)

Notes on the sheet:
Microcontroller
MPU6050
USB
Bluetooth-HC-05
